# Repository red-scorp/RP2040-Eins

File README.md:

```
 ______    _______  _______  _______  _   ___  _______         _______  ___   __    _  _______ 
|    _ |  |       ||       ||  _    || | |   ||  _    |       |       ||   | |  |  | ||       |
|   | ||  |    _  ||____   || | |   || |_|   || | |   | ____  |    ___||   | |   |_| ||  _____|
|   |_||_ |   |_| | ____|  || | |   ||       || | |   ||____| |   |___ |   | |       || |_____ 
|    __  ||    ___|| ______|| |_|   ||___    || |_|   |       |    ___||   | |  _    ||_____  |
|   |  | ||   |    | |_____ |       |    |   ||       |       |   |___ |   | | | |   | _____| |
|___|  |_||___|    |_______||_______|    |___||_______|       |_______||___| |_|  |__||_______|
```

# RP2040-Eins Project

The **RP2040-Eins** project aims to create a replacement for the Arduino UNO R3 or Arduino M0 using the RP2040 MCU.

## RP2040-Eins Board

The **RP2040-Eins** board is a 4-layer design intended to accommodate the popular Raspberry Pi RP2040 MCU within the standard Arduino UNO R3 footprint.

This board is crafted in Germany, and its name, "RP2040-Eins", incorporates the German word "Eins" (pronounced as "eye-ns"), which translates to "one". This name choice reflects the use of the same form-factor as the Arduino "Uno", which means "one" in Italian.

Preview:

You can view the [Schematics in PDF format](doc/RP2040-Eins.pdf) for detailed information.

STEP 3D file is available [with pins](doc/RP2040-Eins.step).

Features:

- Arduino UNO compatible pinout
- Partially compatible with Arduino Nano RP2040 Connect pinout
- Dual-core Cortex-M0+ Raspberry Pi RP2040
- 21 GPIO pins, including 4 analog inputs
- USB Type-C connector
- JTAG and DBG debugging connectors
- LDO-based 5V and 3.3V power supply with a maximum 12V input
- Supports both SOIC and WSON 16MB flash packages
- Includes power, user and RGB LEDs

CAM files, as well as the BOM and CPL files for JLCPCB, are available.

### Board Pinout

Following pinout is used for the board:

| Board Pin | RP2040 Pin | Function | Notes |
| --------- | ---------- | -------- | ----- |
| D0        | GPIO1      | UART0 TX |       |
| D1        | GPIO0      | UART0 RX |       |
| D2        | GPIO25     |          |       |
| D3        | GPIO15     |          |       |
| D4        | GPIO16     |          |       |
| D5        | GPIO17     |          |       |
| D6        | GPIO18     |          |       |
| D7        | GPIO19     |          |       |
| D8        | GPIO20     |          |       |
| D9        | GPIO21     |          |       |
| D10       | GPIO5      | SS       |       |
| D11       | GPIO7      | MOSI     |       |
| D12       | GPIO4      | MISO     |       |
| D13       | GPIO6      | SCK      | LED   |
| D14 A0    | GPIO26     |          |       |
| D15 A1    | GPIO27     |          |       |
| D16 A2    | GPIO28     |          |       |
| D17 A3    | GPIO29     |          |       |
| D18       | GPIO12     | SDA      |       |
| D19       | GPIO13     | SCL      |       |
| D20       | GPIO22     |          |       |
| D21       | GPIO23     |          |       |
| LED_R     | GPIO9      |          |       |
| LED_G     | GPIO10     |          |       |
| LED_B     | GPIO11     |          |       |

## Version History

This board exists in a single LDO-based flavor. If you want to use a Buck-based version of this board, please contact me directly.

Each version of the board listed below is tagged in the repository. You can use the tag to checkout the repository to the specific version.

### v1.0b4 - 09.02.2024

Last testing release.

- Fixed SPI connector pins layout.
- Renamed Arduino pins as Dxx an added GPIO pin names at the back as Gxx.
- Added 2.54mm 3-pin DBG connector.

### v1.0b3 - 21.11.2023

Third testing release.

- Moved BOOTSEL button to the edge of the board for easier access when shield is attached.
- Moved QSPI flash closer to the MCU.
- Added Arduino code examples for RGB LED.
- Rearranged routing of several lines.
- Added fancy board name label.
- Added white silkscreen under the LEDs to add light reflection.
- Moved text on the back of the board a bit.
- Removed pull-up resistor from SWCLK line.

### v1.0b2 - 04.11.2023

Second testing release.

- Added MOSFETs for RGB LED to make it work similarly to user LED.
- Moved few components around.
- Added QR code to the back of the board.

### v1.0b1 - 15.10.2023

Initial release for testing purposes.

## Code Examples

Following code examples are available:

Only Adruino SDK:
- ``src/arduino/rgb_led/rotation_blink.ino`` - blinks RGB LED in rotation individually
- ``src/arduino/rgb_led/rotation_fade.ino`` - fades RGB LED in rotation individually
- ``src/arduino/rgb_led/rotation_fade2.ino`` - fades RGB LED in rotation from one color to another

Arduino SDK with FreeRTOS:
- ``src/arduino/rgb_led/freertos_fade.ino`` - fades RGB LED in rotation individually using FreeRTOS

Please use latest official version of [earlephilhower/arduino-pico](https://github.com/earlephilhower/arduino-pico) and select "RP2040-Eins" board as a target.

## Links

- [Raspberry Pi RP2040 information page](https://www.raspberrypi.com/documentation/microcontrollers/rp2040.html).
- [Arduino UNO R3 information page](https://docs.arduino.cc/retired/boards/arduino-uno-rev3-with-long-pins).
- [Arduino SDK for RP2040 board](https://github.com/earlephilhower/arduino-pico).

## How to Help

Your contributions as code, resources, or finances are welcome! Please contact me directly via email at andriy.golovnya@gmail.com or through my [GitHub profile](https://github.com/red-scorp).

If you'd like to make a financial contribution, you can donate via [PayPal](http://paypal.me/redscorp) or [Ko-Fi](http://ko-fi.com/redscorp). Your support is greatly appreciated.

Thanks in advance!

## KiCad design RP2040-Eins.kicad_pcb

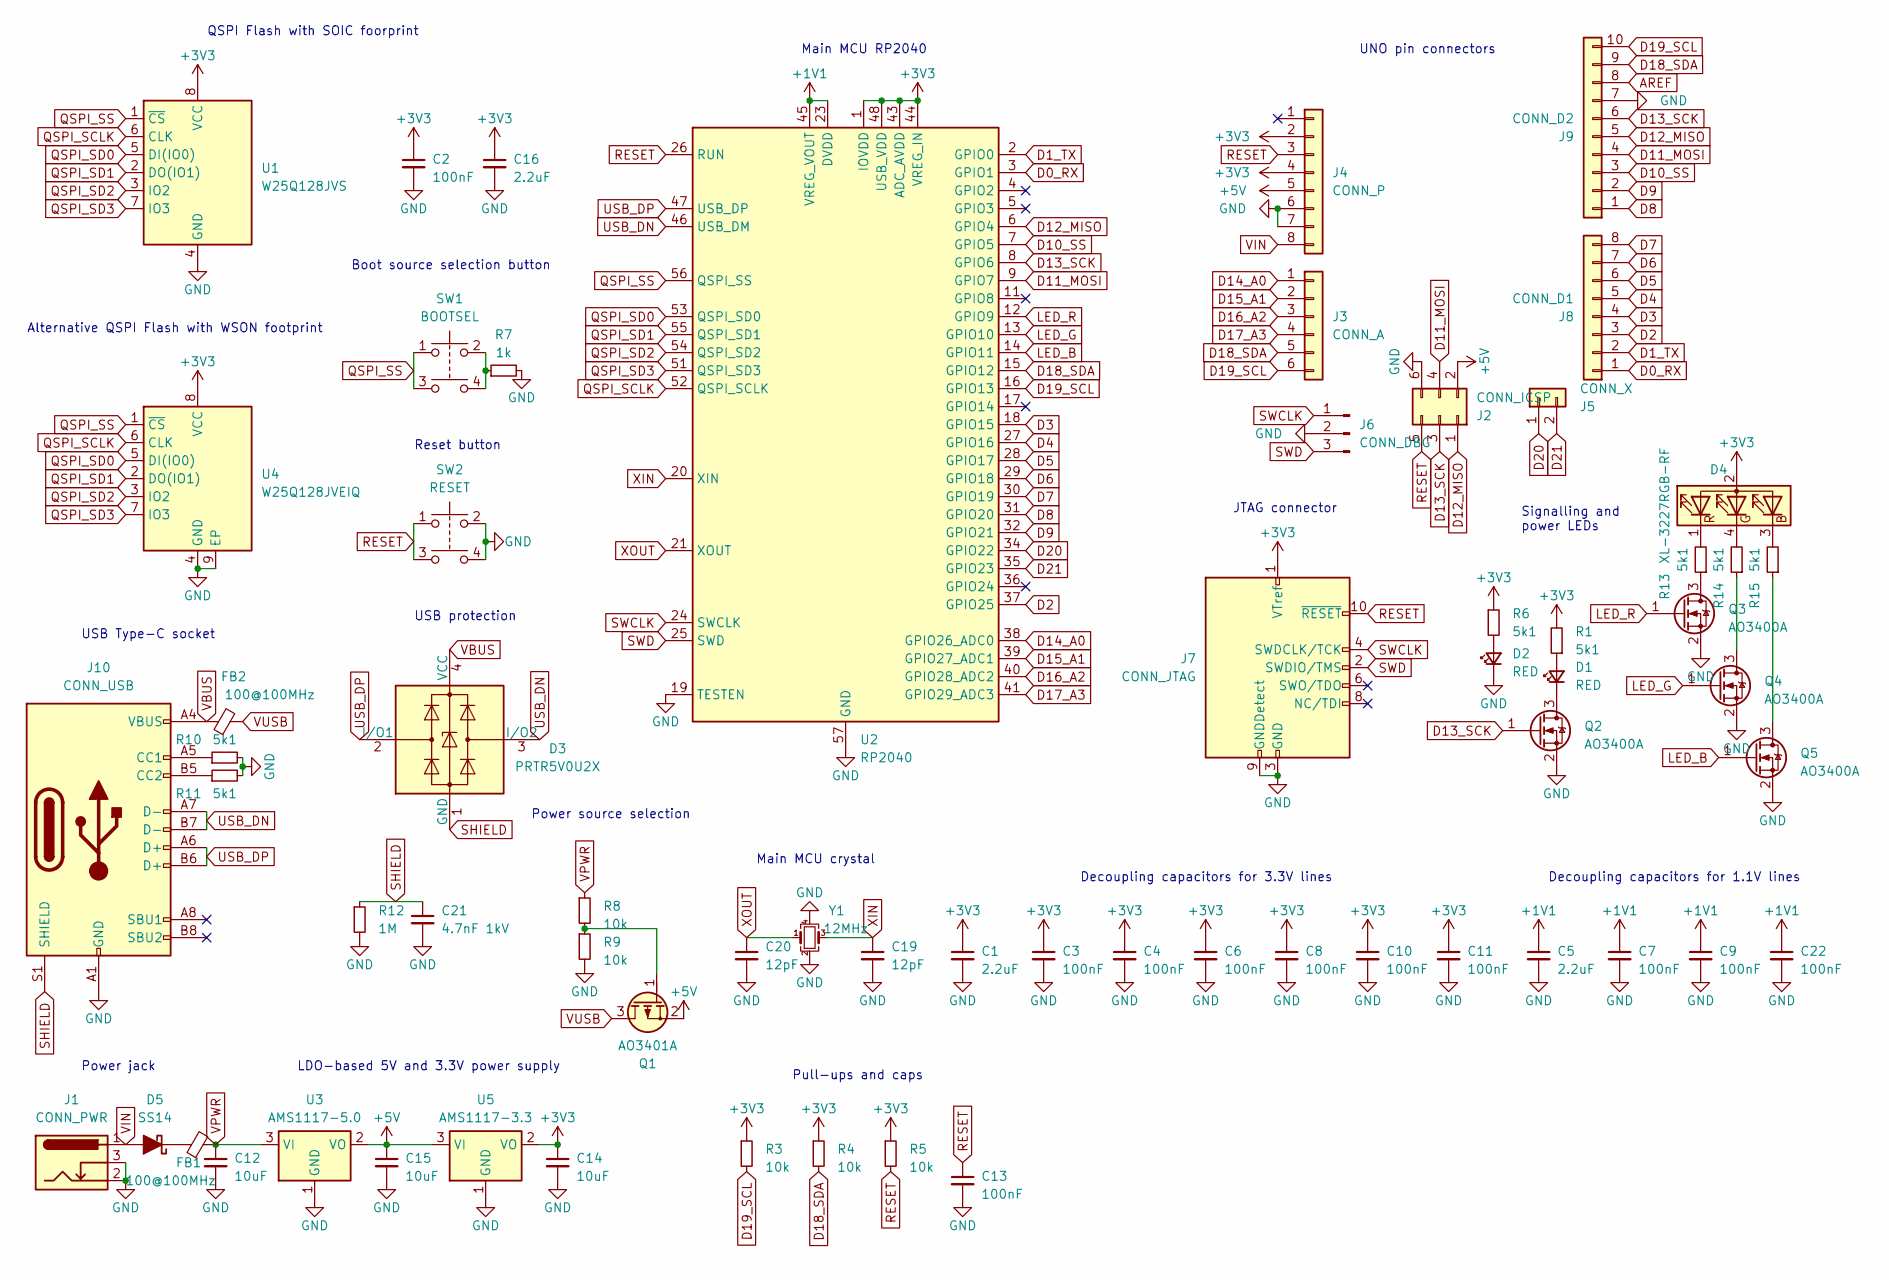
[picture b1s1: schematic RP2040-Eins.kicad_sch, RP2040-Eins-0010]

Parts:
C1, C5, C16: 2.2uF; C_0603_1608Metric
C2, C3, C4, C6, C7, C8, C9, C10, C11, C13, C22: 100nF; C_0402_1005Metric
C12, C14, C15: 10uF; C_0805_2012Metric
C19, C20: 12pF; C_0402_1005Metric
C21: 4.7nF 1kV; C_1206_3216Metric
D1, D2: RED; LED_0603_1608Metric
D3: PRTR5V0U2X; SOT-143
D4: XL-3227RGB-RF; LED_RGB_1210
D5: SS14; D_DO-214AC_SMA
FB1, FB2: 100@100MHz; L_0805_2012Metric
J1: CONN_PWR; BarrelJack_Horizontal
J2: CONN_ICSP; PinHeader_2x03_P2.54mm_Vertical
J3: CONN_A; PinSocket_1x06_P2.54mm_Vertical
J4: CONN_P; PinSocket_1x08_P2.54mm_Vertical
J5: CONN_X; PinHeader_1x02_P2.54mm_Vertical
J6: CONN_DBG; PinHeader_1x03_P2.54mm_Vertical
J7: CONN_JTAG; PinHeader_2x05_P1.27mm_Vertical
J8: CONN_D1; PinSocket_1x08_P2.54mm_Vertical
J9: CONN_D2; PinSocket_1x10_P2.54mm_Vertical
J10: CONN_USB; USB_C_Receptacle_HRO_TYPE-C-31-M-12
Q1: AO3401A; SOT-23
Q2, Q3, Q4, Q5: AO3400A; SOT-23
R1, R6, R10, R11, R13, R14, R15: 5k1; R_0402_1005Metric
R3, R4, R5, R8, R9: 10k; R_0402_1005Metric
R7: 1k; R_0402_1005Metric
R12: 1M; R_0603_1608Metric
SW1: BOOTSEL; Button_Tact_Sqkg
SW2: RESET; Button_Tact_Sqkg
U1: W25Q128JVS; SOIC-8_5.23x5.23mm_P1.27mm
U2: RP2040; QFN-56-1EP_7x7mm_P0.4mm_EP3.2x3.2mm
U3: AMS1117-5.0; SOT-223-3_TabPin2
U4: W25Q128JVEIQ; WSON-8-1EP_6x5mm_P1.27mm_EP3.4x4.3mm
U5: AMS1117-3.3; SOT-223-3_TabPin2
Y1: 12MHz; Crystal_SMD_3225-4Pin_3.2x2.5mm

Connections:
+1V1: C5.1, C7.1, C9.1, C22.1, U2.23 (DVDD), U2.45 (VREG_VOUT), U2.50 (DVDD)
+3V3: C1.1, C2.1, C3.1, C4.1, C6.1, C8.1, C10.1, C11.1, C14.1, C16.1, D4.2 (A), J4.2, J4.4, J7.1 (VTref), R1.2, R3.1, R4.1, R5.1, R6.1, U1.8 (VCC), U2.1 (IOVDD), U2.10 (IOVDD), U2.22 (IOVDD), U2.33 (IOVDD), U2.42 (IOVDD), U2.43 (ADC_AVDD), U2.44 (VREG_IN), U2.48 (USB_VDD), U2.49 (IOVDD), U4.8 (VCC), U5.2 (VO)
+5V: C15.1, J2.2, J4.5, Q1.2 (S), U3.2 (VO), U5.3 (VI)
AREF: J9.8
D0_RX: J8.1, U2.3 (GPIO1)
D1_TX: J8.2, U2.2 (GPIO0)
D2: J8.3, U2.37 (GPIO25)
D3: J8.4, U2.18 (GPIO15)
D4: J8.5, U2.27 (GPIO16)
D5: J8.6, U2.28 (GPIO17)
D6: J8.7, U2.29 (GPIO18)
D7: J8.8, U2.30 (GPIO19)
D8: J9.1, U2.31 (GPIO20)
D9: J9.2, U2.32 (GPIO21)
D10_SS: J9.3, U2.7 (GPIO5)
D11_MOSI: J2.4, J9.4, U2.9 (GPIO7)
D12_MISO: J2.1, J9.5, U2.6 (GPIO4)
D13_SCK: J2.3, J9.6, Q2.1 (G), U2.8 (GPIO6)
D14_A0: J3.1, U2.38 (GPIO26_ADC0)
D15_A1: J3.2, U2.39 (GPIO27_ADC1)
D16_A2: J3.3, U2.40 (GPIO28_ADC2)
D17_A3: J3.4, U2.41 (GPIO29_ADC3)
D18_SDA: J3.5, J9.9, R4.2, U2.15 (GPIO12)
D19_SCL: J3.6, J9.10, R3.2, U2.16 (GPIO13)
D20: J5.1, U2.34 (GPIO22)
D21: J5.2, U2.35 (GPIO23)
GND: C1.2, C2.2, C3.2, C4.2, C5.2, C6.2, C7.2, C8.2, C9.2, C10.2, C11.2, C12.2, C13.2, C14.2, C15.2, C16.2, C19.2, C20.2, C21.2, C22.2, D2.1 (K), J1.2, J1.3, J2.6, J4.6, J4.7, J6.2, J7.3 (GND), J7.5 (GND), J7.9 (GNDDetect), J9.7, J10.A1 (GND), J10.A12 (GND), J10.B1 (GND), J10.B12 (GND), Q2.2 (S), Q3.2 (S), Q4.2 (S), Q5.2 (S), R7.2, R9.2, R10.2, R11.2, R12.2, SW2.2, SW2.4, U1.4 (GND), U2.19 (TESTEN), U2.57 (GND), U3.1 (GND), U4.4 (GND), U4.9 (EP), U5.1 (GND), Y1.2, Y1.4
LED_B: Q5.1 (G), U2.14 (GPIO11)
LED_G: Q4.1 (G), U2.13 (GPIO10)
LED_R: Q3.1 (G), U2.12 (GPIO9)
unnamed: D1.2 (A), R1.1
unnamed: D1.1 (K), Q2.3 (D)
unnamed: D2.2 (A), R6.2
unnamed: D4.3 (BK), R15.2
unnamed: D4.4 (GK), R14.2
unnamed: D4.1 (RK), R13.2
unnamed: D5.1 (K), FB1.1
unnamed: J10.A5 (CC1), R10.1
unnamed: J10.B5 (CC2), R11.1
unnamed: Q1.1 (G), R8.2, R9.1
unnamed: Q3.3 (D), R13.1
unnamed: Q4.3 (D), R14.1
unnamed: Q5.3 (D), R15.1
unnamed: R7.1, SW1.2, SW1.4
QSPI_SCLK: U1.6 (CLK), U2.52 (QSPI_SCLK), U4.6 (CLK)
QSPI_SD0: U1.5 (DI(IO0)), U2.53 (QSPI_SD0), U4.5 (DI(IO0))
QSPI_SD1: U1.2 (DO(IO1)), U2.55 (QSPI_SD1), U4.2 (DO(IO1))
QSPI_SD2: U1.3 (IO2), U2.54 (QSPI_SD2), U4.3 (IO2)
QSPI_SD3: U1.7 (IO3), U2.51 (QSPI_SD3), U4.7 (IO3)
QSPI_SS: SW1.1, SW1.3, U1.1 (~CS), U2.56 (QSPI_SS), U4.1 (~CS)
RESET: C13.1, J2.5, J4.3, J7.10 (~RESET), R5.2, SW2.1, SW2.3, U2.26 (RUN)
SHIELD: C21.1, D3.1 (GND), J10.S1 (SHIELD), R12.1
SWCLK: J6.1, J7.4 (SWDCLK/TCK), U2.24 (SWCLK)
SWD: J6.3, J7.2 (SWDIO/TMS), U2.25 (SWD)
USB_DN: D3.3 (I/O2), J10.A7 (D-), J10.B7 (D-), U2.46 (USB_DM)
USB_DP: D3.2 (I/O1), J10.A6 (D+), J10.B6 (D+), U2.47 (USB_DP)
VBUS: D3.4 (VCC), FB2.1, J10.A4 (VBUS), J10.A9 (VBUS), J10.B4 (VBUS), J10.B9 (VBUS)
VIN: D5.2 (A), J1.1, J4.8
VPWR: C12.1, FB1.2, R8.1, U3.3 (VI)
VUSB: FB2.2, Q1.3 (D)
XIN: C19.1, U2.20 (XIN), Y1.3
XOUT: C20.1, U2.21 (XOUT), Y1.1

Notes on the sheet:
USB protection
Alternative QSPI Flash with WSON footprint
UNO pin connectors
Main MCU RP2040
Power source selection
Power jack
Decoupling capacitors for 3.3V lines
Main MCU crystal
Decoupling capacitors for 1.1V lines
Pull-ups and caps
Signalling and power LEDs
JTAG connector
Reset button
USB Type-C socket
Boot source selection button
LDO-based 5V and 3.3V power supply
QSPI Flash with SOIC foorprint

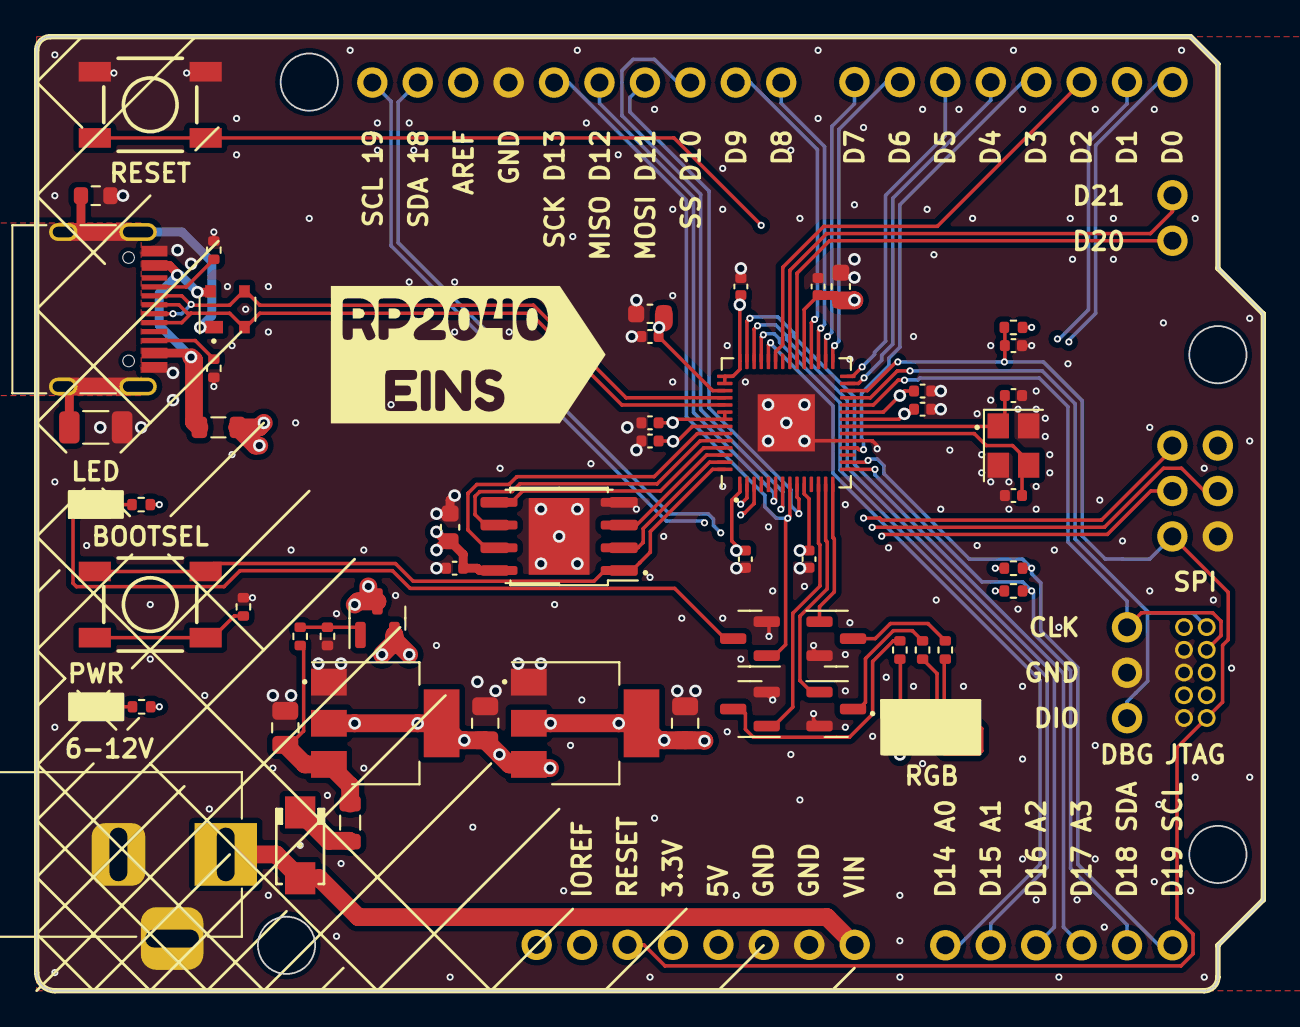
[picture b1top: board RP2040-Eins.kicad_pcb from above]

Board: 4 copper layers, 68.6 x 53.3 mm, 66 parts (1 on the bottom side), 61 nets.

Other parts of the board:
G1: QR-CODE; LOGO
G2: BOARD-LABEL; kibuzzard-654A67CC

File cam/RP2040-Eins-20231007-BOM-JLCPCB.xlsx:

Qty | Designator | Footprint | JLCPCB Part# | Comment
1 | Q1 | SOT-23 | C15127 | AO3401A
3 | C15,C14,C12 | 0805 | C15850 | 10uF
2 | FB2,FB1 | 0805 | C1015 | GZ2012D101TF
3 | C5,C16,C1 | 0603 | C1604 | 2.2uF
6 | R3,R2,R8,R9,R5,R4 | 0402 | C25744 | 10k
1 | U1 | SOIC-8-208mil | C97521 | W25Q128JVS
1 | SW1,SW2 | SMD | C318884 | TS-1187A-B-A-B
1 | J3 | Plugin,P=2.54mm | C2935977 | CONN_A
1 | J1 | Plugin | C16214 | CONN_PWR
7 | R14,R11,R13,R6,R1,R15,R10 | 0402 | C25905 | 5k1
1 | U3 | SOT-223 | C6187 | AMS1117-5.0
1 | D4 | 1210 | C965844 | RGB
1 | Y1 | SMD3225-4P | C9002 | 12MHz
11 | C7,C13,C6,C22,C3,C11,C2,C8,C4,C9,C10 | 0402 | C1525 | 100nF
1 | D5 | SMA(DO-214AC) | C2480 | SS14
1 | U2 | LQFN-56(7x7) | C2040 | RP2040
2 | C20,C19 | 0402 | C1547 | 12pF
2 | D1,D2 | 0603 | C2286 | RED
1 | J4 | Plugin,P=2.54mm | C429957 | CONN_P
1 | Q2 | SOT-23-3L | C20917 | AO3400A
1 | J2 | Plugin,P=2.54mm | C390684 | CONN_ICSP
1 | J9 | Plugin,P=2.54mm | C2935981 | CONN_D2
1 | J7 | SMD,P=1.27mm | C721880 | JTAG
1 | U4 | WSON-8-EP(6x8) | C2456297 | W25Q128JVEIQ TR
1 | R7 | 0402 | C11702 | 1k
1 | J10 | SMD | C2689844 | CONN_USB
1 | U5 | SOT-223-3 | C6186 | AMS1117-3.3
1 | C21 | 1206 | C377102 | 4.7nF 1kV
1 | D3 | SOT-143 | C5158049 | PRTR5V0U2X
1 | J8 | Plugin,P=2.54mm | C429957 | CONN_D1
1 | R12 | 0603 | C279988 | 1M
1 | J5 | Plugin,P=2.54mm | C2833329 | CONN_X

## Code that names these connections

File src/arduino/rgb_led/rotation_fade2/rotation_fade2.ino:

/**
 * @file rotation_fade2.ino
 * @brief Fade the RGB LED in rotation
 *
 * This program fades the RGB LED in rotation.
 * The LED is fades from red to green, then from green to blue, and then from blue to red.
 * This process is repeated.
 *
 * @date 2023/12/28
 * @version 1.0.0
 */

#include <Arduino.h>

/* RGB LED pin numbers are defined in the rp2040 SDK as PIN_LED_R, PIN_LED_G and PIN_LED_B when you select RP2040-Eins as a target board */

const int fadeDuration = 1000; // 1 second fade duration

void setup() {
  // Set the pin modes for the LEDs as outputs
  pinMode(PIN_LED_R, OUTPUT);
  pinMode(PIN_LED_G, OUTPUT);
  pinMode(PIN_LED_B, OUTPUT);
}

void loop() {
  // Rotate the fade colors
  fadeLED(PIN_LED_R, PIN_LED_G);
  fadeLED(PIN_LED_G, PIN_LED_B);
  fadeLED(PIN_LED_B, PIN_LED_R);
}

void fadeLED(int fromPin, int toPin) {
  // Fade on LED on and fade another LED off
  for (int brightness = 0; brightness <= 255; brightness++) {
    analogWrite(fromPin, 255 - brightness);
    analogWrite(toPin, brightness);
    delay(fadeDuration / 255);
  }
}

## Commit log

2023-09-20 Added LDO power and UNO pinout
2023-09-21 Added few components
2023-09-22 Added more components to schematics
2023-09-22 Added ICSP connector. Changed JTAG connector footprint.
2023-09-22 Removed libraries.
2023-09-23 Added board edge
2023-09-24 Exchanged Arduino board shape with separate connectors
2023-09-24 Added quartz caps. Moved stuff around.
2023-09-25 Switched to USB-C with all stuff around it.
2023-09-26 Moved stuff around
2023-09-26 Added polarity reversion protection diode
2023-09-29 Added few traces
2023-09-30 Put schottky diode instead of normal one.
2023-09-30 Simplified the schematics a bit
2023-09-30 Added ferrite beads. Changed power routing.
2023-10-03 Added RGB LED
2023-10-03 Fixed RGB LED orientation
2023-10-05 Added front silkscreen labels
2023-10-05 Added back side silk labels
2023-10-05 Added board description on the back silk.
2023-10-06 Rewired some traces away from power layer. Removed pin labels from bottom side.
2023-10-06 Added few board decorations
2023-10-06 Added README.md prototype
2023-10-07 Generated CAM files
2023-10-07 Generated PDF preview
2023-10-07 Generated STEP file
2023-10-07 Generated PNG preview
2023-10-08 Added aggregate BoM file (includes both WSON and SOIC flash parts)
2023-10-08 Renamed BOM file
2023-10-08 Added aggregate CPL file (includes both WSON and SOIC flash parts)
2023-10-08 Added missing THT components
2023-10-08 Split BoM and CPL into WSON and SOIC versions for easier ordering
2023-10-08 Rotated several components to fit manufacturer's placement
2023-10-08 Added center line marker for pins headers
2023-10-14 Adjusted connector positions.
2023-10-15 Moves few stuff around
2023-10-15 Generated PDF schematics
2023-10-15 Added v1.0b1 PNG preview
2023-10-16 Fixed 1M resistor code
2023-10-21 Added mosfets for RGB LED. Moved staff around.
2023-11-02 Moved stuff around.
2023-11-03 Added QR Code on the back side.
2023-11-04 Generated STEP 3D file
2023-11-04 Generated BOM and CPL files
2023-11-04 Generated PNG preview images
2023-11-04 Updated documentation
2023-11-07 Moved BOOTSEL button closer to the front edge of the board. Moved stuff around to fit better.
2023-11-07 Added fancy label. Moved some texts around.
2023-11-07 Moved QSPI flash chip closer to the MCU
2023-11-07 Added white color under the LEDs to add light reflection.
2023-11-08 Simplified routing a bit.
2023-11-09 Added rotation_blink.ino arduino example.
2023-11-09 Added constant macro for blink duration.
2023-11-09 Added rotation_fade.ino arduino example.
2023-11-09 Added rotation_fade2.ino arduino example.
2023-11-09 Fixed end of title comment.
2023-11-09 Added arduino examples into README.md
2023-11-09 Fixed example code. Added comments.
2023-11-11 Added code styling to code file path
2023-11-12 Changed 6p connector id
2023-11-12 Updated release date information
2023-11-12 Generated PDF schematic
2023-11-12 Generated PNG previews
2023-11-12 Updated board v1.0b3 description
2023-11-18 Selected another equivalent parts to cover shortage
2023-11-21 Removed pull-up resistor for SWDCLK line.
2023-11-30 Modified header to comply fully to doxygen comment format
2023-11-30 Added FreeRTOS example
2023-11-30 Renamed fade duration variables
2023-11-30 Used proper FreeRTOS delay timer definition
2023-12-03 Fixed header name
2023-12-03 Fixed typo
2023-12-10 Added FUNDING.yml file
2023-12-14 Fixed README a bit
2023-12-23 Fixed SPI connector pins layout
2023-12-23 Updated README.md with b4
2023-12-24 Use build-in FreeRTOS library instead of third party library
2023-12-25 Fixed doxygen comments
2023-12-28 Checked date information
2023-12-29 Added board pinout information
2023-12-30 Renamed Arduino pins as Dxx. Added GPIO pin names at the back as Gxx.
2023-12-30 Updated README.md with last commit changes
2023-12-30 Added few missing periods in README.md
2024-01-02 Added release dates and tags information to README.md
2024-01-12 Added 2.54mm 3-pin DBG connector
2024-01-12 Generated STEP 3D model

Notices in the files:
RP2040-Eins.kicad_pcb:
(c) 2023-2024 Andriy Golovnya
